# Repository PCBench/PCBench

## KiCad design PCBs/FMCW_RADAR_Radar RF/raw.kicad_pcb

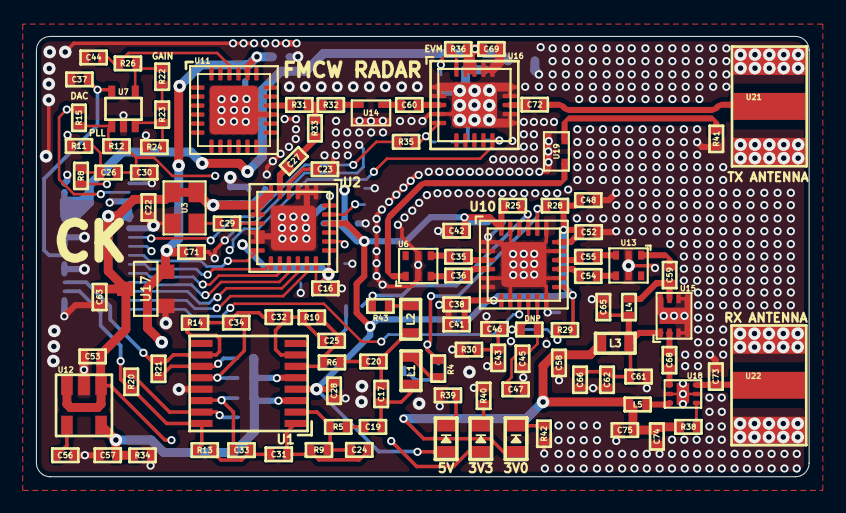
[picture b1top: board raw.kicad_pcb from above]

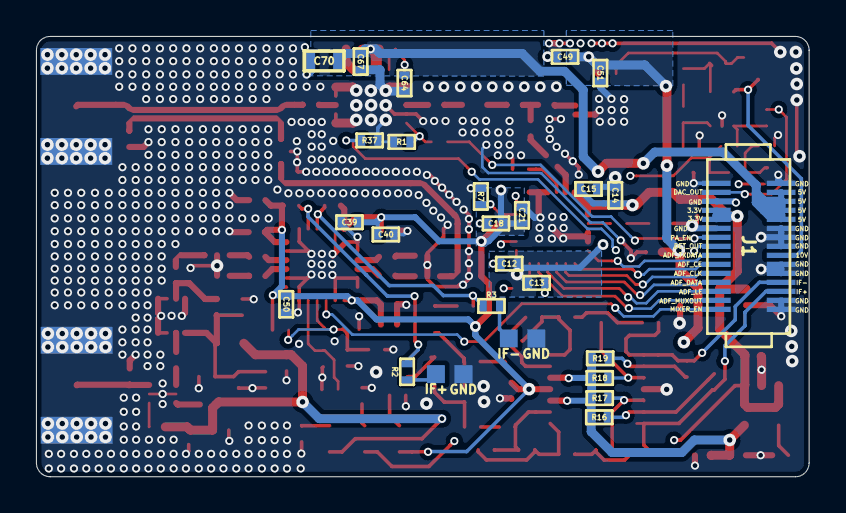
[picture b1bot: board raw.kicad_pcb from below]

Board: 4 copper layers, 42.9 x 24.5 mm, 143 parts (28 on the bottom side), 92 nets.

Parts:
3V0, 3V3, 5V: Led_Diode; Diode_0603
C12, C13, C14, C21, C22, C28, C37, C38, C39, C40, C43, C45, C46, C48, C50, C51, C52, C53, C64, C67, C69, C74, C75: 100nF; SMD_0402
C15, C16, C18, C59, C68: 18pF; SMD_0402
C17: 2.2nF; SMD_0402
C19, C20, C26: 330nF; SMD_0402
C23, C41, C42, C47, C65: 100pF; SMD_0402
C24, C25, C35, C36, C54, C55, C62: 10pF; SMD_0402
C27: 2pF; SMD_0402
C29, C31, C32, C33, C34, C44: 470pF; SMD_0402
C30, C56, C61: 10nF; SMD_0402
C49, C57, C63, C71: 2.2uF; SMD_0402
C58, C66: DNP; SMD_0402
C60, C72: 1000pF; SMD_0402
C70: 10uF; SMD_0603
C73: 0.5pF; SMD_0402
DNP: DNP; SMD_0402
GND: GND; SolderPad_1_1.5mm_SMD_Rectangle
GND#2: GND; SolderPad_1_1.5mm_SMD_Rectangle
IF+: IF+_PAD; SolderPad_1_1.5mm_SMD_Rectangle
IF-: IF-_PAD; SolderPad_1_1.5mm_SMD_Rectangle
J1: Connector_02x15; PinHeader_2x15_DF12B(5.0)-30DP-0.5V(86)
L1, L2: 2.2uH; SMD_0603
L3: BLM18PG181SN1D; SMD_0603
L4: LQW15AN9N9J80D; SMD_0402
L5: 0.6nH; SMD_0402
R1, R16, R19, R29, R39, R40, R42: 1K; SMD_0402
R2, R3, R15, R30: DNP; SMD_0402
R4, R12, R22, R35, R43: 0; SMD_0402
R5, R6: 549; SMD_0402
R7: 5.49K; SMD_0402
R8: 69.8; SMD_0402
R9, R10, R34: 10K; SMD_0402
R11: 240; SMD_0402
R13, R14: 910; SMD_0402
R17, R18: 130; SMD_0402
R20, R21: 4.99K; SMD_0402
R23, R24, R26: 4.7K; SMD_0402
R25, R28, R41: 50; SMD_0402
R31, R32, R33: 18; SMD_0402
R36: 0 to 27; SMD_0402
R37: 30K; SMD_0402
R38: 100; SMD_0402
U1: LT6232; SSOP16_3.9x4.9mm_P0.635mm
U2: ADF4158; LFCSP24_4x4mm_P0.5mm_1EXP_2.5x2.5mm
U3: SG-210STF; Crystal_2.5x2mm
U4, U9, U23: MITERED_BEND; Mitered_Bend_0.34mm_90
U5: MITERED_BEND; Mitered_Bend_0.34mm_45
U6, U13: 5400BL15B050E; Balun_5400BL15B050E
U7: TLV172; SC70_5
U8: MITERED_BEND; Mitered_Bend_0.34mm_45_Mirrored
U10: ADL5801; LFCSP24_4x4mm_P0.5mm_1EXP_2.5x2.5mm
U11: HMC431LP4; QFN24_4x4mm_P0.5mm_1EXP_2.7x2.7mm
U12: LDS3985; SOT23_5
U14, U19: PAT1220-C-6DB; PAT1220_6dB
U15: TRF37A73; WSON8_2x2mm_P0.5mm_1EXP_0.9x1.6mm
U16: TQP5523; QFN20_4x4mm_P0.5mm_1EXP_2.5x2.5mm
U17: MCP1700; SOT23_3
U18: SKY65404; SKY65404_31
U20: Directional_Coupler; Directional_Coupler_15dB
U21, U22: SMA_Connector

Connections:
25MHz: C29.1, U2.9
+2V5: C57.1, R16.2, R17.2, R18.1, R19.2, R34.1, U1.3, U1.5, U12.5
+3V0: 3V0.2, C49.1, C51.1, C58.1, C71.1, C74.1, C75.1, L3.1, L5.2, R38.1, U11.20, U17.2
+3V3: 3V3.2, C12.1, C13.1, C14.1, C15.1, C16.1, C22.1, C53.1, C63.1, J1.4, J1.5, U2.6, U2.7, U2.8, U2.18, U2.19, U3.1, U3.4, U12.1, U12.3, U17.3
+5V: 5V.2, C18.1, C21.1, C28.2, C38.2, C39.2, C40.2, C41.2, C42.2, C48.2, C50.2, C52.1, C67.2, C69.2, C70.2, J1.26, J1.27, J1.28, J1.29, R25.1, R28.2, R29.1, R36.1, U1.4, U2.22, U10.7, U10.13, U10.18, U10.24, U16.18, U16.19
+10V: C37.1, J1.22, U7.5
ADF_CE: J1.10, U2.13
ADF_CLK: J1.11, U2.14
ADF_DATA: J1.12, U2.15
ADF_LE: J1.13, U2.16
ADF_MUXOUT: J1.14, U2.17
ADF_TXDATA: J1.9, U2.12
DAC_OUT1: J1.2, R15.1
DET_OUT: J1.8, R37.1, U16.10
GND: C12.2, C13.2, C14.2, C15.2, C16.2, C18.2, C21.2, C22.2, C23.2, C28.1, C30.2, C37.2, C38.1, C39.1, C40.1, C41.1, C42.1, C43.1, C44.2, C45.1, C46.1, C47.1, C48.1, C49.2, C50.1, C51.2, C52.2, C53.2, C56.2, C57.2, C58.2, C61.2, C62.2, C63.2, C64.2, C65.2, C66.2, C67.1, C69.1, C70.1, C71.2, C73.2, C74.2, C75.2, GND.1, GND#2.1, J1.1, J1.3, J1.6, J1.16, J1.17, J1.20, J1.21, J1.23, J1.24, J1.25, J1.30, R1.2, R7.2, R11.1, R24.2, R30.2, R34.2, R37.2, R39.2, R40.2, R41.2, R42.2, U1.13, U2.1, U2.2, U2.3, U2.10, U2.11, U2.25, U3.2, U6.2, U6.5, U7.2, U10.1, U10.2, U10.5, U10.6, U10.8, U10.12, U10.14, U10.17, U10.19, U10.23, U10.25, U11.15, U11.25, U12.2, U13.2, U13.5, U14.3, U15.3, U15.4, U15.5, U15.6, U15.8, U15.9, U16.1, U16.2, U16.4, U16.11, U16.12, U16.14, U16.15, U16.16, U16.17, U16.21, U17.1, U18.2, U18.5, U18.7, U19.3, U21.2, U21.3, U21.4, U21.5, U22.2, U22.3, U22.4, U22.5
IF+: R2.1, R4.1, R28.1, U10.20
IF-: R3.2, R25.2, R43.2, U10.21
IFN_Filtered: J1.19, R14.2, R21.1, U1.10
IFP_Filtered: J1.18, R13.1, R20.1, U1.16
MIXER_ENB: J1.15, U10.9
MIXER_LO: U4.2, U6.1
unnamed: C17.1, C19.2, L1.2
unnamed: C17.2, C20.2, L2.2
unnamed: C19.1, R5.1
unnamed: C20.1, R6.1
unnamed: C23.1, U2.4
unnamed: C24.1, C31.2, R9.2, U1.1
unnamed: C24.2, R5.2, R9.1, U1.2
unnamed: C25.1, C32.2, R10.2, U1.7
unnamed: C25.2, R6.2, R10.1, U1.6
unnamed: C26.1, C30.1, R12.1, U2.24
unnamed: C26.2, R8.2, R11.2
unnamed: C27.1, U2.5
unnamed: C27.2, R33.2
unnamed: C29.2, U3.3
unnamed: C31.1, C33.2, R13.2
unnamed: C32.1, C34.2, R14.1
unnamed: C33.1, R17.1, U1.14
unnamed: C34.1, R18.2, U1.12
unnamed: C35.1, U10.3
unnamed: C35.2, U6.4
unnamed: C36.1, U10.4
unnamed: C36.2, U6.3
unnamed: C43.2, C46.2, DNP.2, R29.2, R30.1, U10.10
unnamed: C44.1, R26.1, U11.22
unnamed: C45.2, C47.2, DNP.1, U10.11
unnamed: C54.1, U13.4
unnamed: C55.1, U13.3
unnamed: C56.1, U12.4
unnamed: C59.1, L4.1, U15.7
unnamed: C59.2, U23.1
unnamed: C60.1, U16.3
unnamed: C60.2, U14.2
unnamed: C61.1, C62.1, C65.1, C66.1, L3.2, L4.2, U15.1
unnamed: C64.1, R36.2, U16.20
unnamed: C68.1, U18.4
unnamed: C68.2, U15.2
unnamed: C72.1, U20.1
unnamed: C72.2, U16.13
unnamed: C73.1, U18.3, U22.1
unnamed: 5V.1, R39.1
unnamed: 3V3.1, R40.1
unnamed: 3V0.1, R42.1
unnamed: L1.1, R4.2
unnamed: L2.1, R43.1
unnamed: L5.1, U18.6
unnamed: R1.1, R35.2, U16.5
unnamed: IF+.1, R2.2
unnamed: IF-.1, R3.1
unnamed: R7.1, U2.23
unnamed: R8.1, U2.20
unnamed: R12.2, R15.2, U7.1
unnamed: R16.1, R20.2, U1.15
unnamed: R19.1, R21.2, U1.11
unnamed: R22.1, R26.2, U7.4
unnamed: R22.2, R23.1
unnamed: R23.2, R24.1, U7.3
unnamed: R31.1, U11.16
unnamed: R31.2, R32.2, R33.1
unnamed: R32.1, U14.1
unnamed: R38.2, U18.1
unnamed: R41.1, U20.4
unnamed: U4.1, U8.1
unnamed: U5.1, U9.1
unnamed: U5.2, U8.2
unnamed: U13.1, U23.2
unnamed: U19.1, U20.3
unnamed: U9.2, U19.2
unnamed: U20.2, U21.1
PA_EN: J1.7, R35.1
RFIN: C54.2, U10.15
RFIP: C55.2, U10.16

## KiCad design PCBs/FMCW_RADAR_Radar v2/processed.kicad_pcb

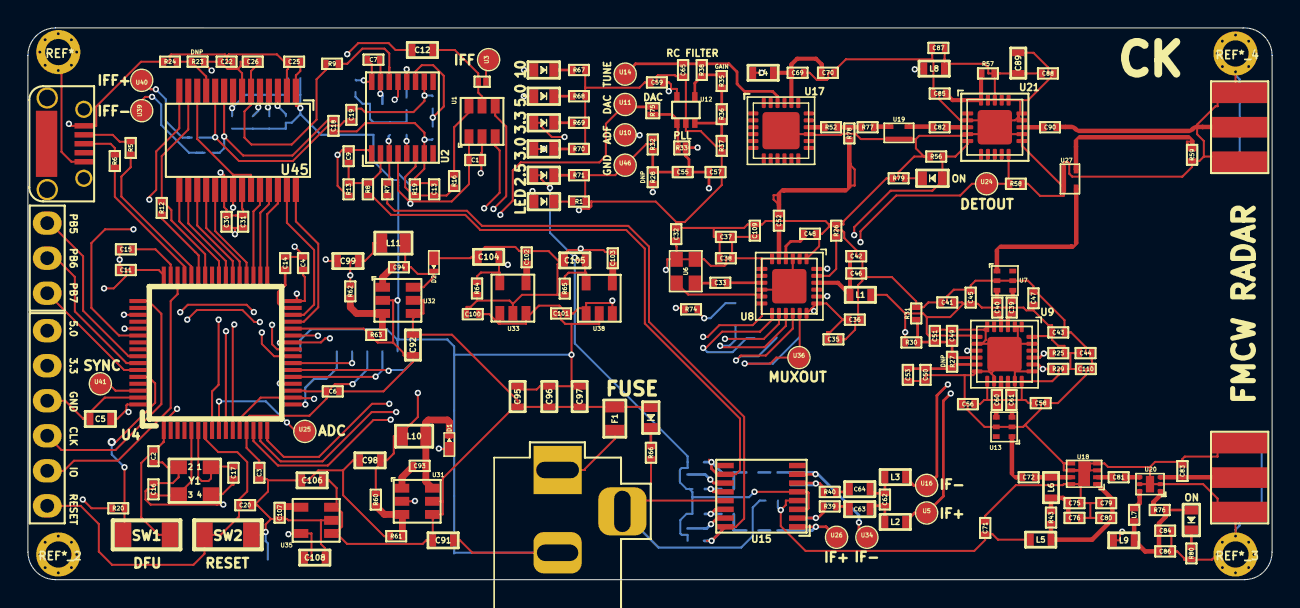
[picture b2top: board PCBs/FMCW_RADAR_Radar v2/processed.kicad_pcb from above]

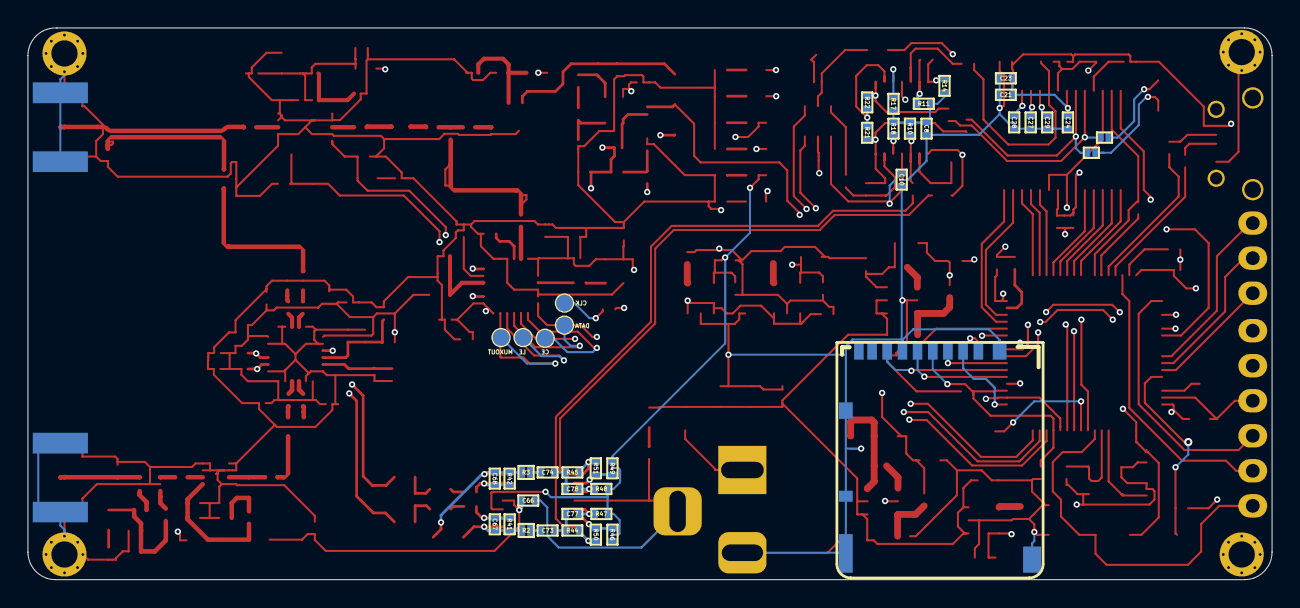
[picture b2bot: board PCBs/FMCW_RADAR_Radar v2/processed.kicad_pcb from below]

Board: 4 copper layers, 90.2 x 40.0 mm, 264 parts (42 on the bottom side), 173 nets.

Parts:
C1, C2, C3, C4, C7, C8, C10, C20, C22, C23, C26, C27, C28, C29, C30, C31, C32, C35, C36, C41, C43, C44, C46, C49, C50, C51, C56, C58, C59, C66, C70, C80, C84, C85, C86, C87, C88, C100, C101, C109, C110: 100nF; SMD_0402
C5, C12, C63, C64, C89, C91, C92, C95, C96, C97, C98, C99: 10uF; SMD_0603
C6, C11, C14, C15, C21, C69: 2.2uF; SMD_0402
C9, C13: 33pF; SMD_0402
C16, C17: 15pF; SMD_0402
C18, C19: 1uF; SMD_0402
C24, C25, C45, C47, C48, C53, C79: 100pF; SMD_0402
C33: 470pF; SMD_0402
C37, C38, C42: 18pF; SMD_0402
C39, C40, C52, C60, C61, C67, C68, C76: 10pF; SMD_0402
C55: 330nF; SMD_0402
C57, C73, C74, C75, C77, C78, C93, C94, C102, C103, C107: 10nF; SMD_0402
C62: 2.2nF; SMD_0402
C65, C71: DNP; SMD_0402
C72, C81, C82, C90: 1nF; SMD_0402
C83: 0.5pF; SMD_0402
C104, C105, C106, C108: 2.2uF; SMD_0603
D1, D2: Diode_Schottky; Diode_SDM2U30CSP_7
D3, D4, D5, D6, D7, D8, D9, D10, D11: Led_Diode; Diode_0603
F1: Fuse; SMD_0805
J1: Connector_01x03; PinHeader_1x3_P2.5mm
J2: USB_MicroB; USB_MicroB_TH
J3: Connector_01x06; PinHeader_1x6_P2.5mm
J4: DC_Jack; BarrelJack
L1, L4, L5, L8, L9: BLM18PG181SN1D; SMD_0603
L2, L3: 2.2uH; SMD_0603
L6: LQW18ANR10J00D; SMD_0603
L7: 0.6nH; SMD_0402
L10, L11: 4.7uH; SMD_0805
R1, R10, R13, R20, R30, R39, R40, R46, R49, R56, R66, R67, R68, R69, R70, R71, R79, R80: 1K; SMD_0402
R2, R3, R24, R33, R35: 0; SMD_0402
R5, R6, R12, R74: 22; SMD_0402
R7, R8, R16, R76: 100; SMD_0402
R9, R11: 2.49K; SMD_0402
R14: 49.9; SMD_0402
R15, R23, R27, R28, R31, R72, R73, R75: DNP; SMD_0402
R17, R19, R36, R37, R63: 4.7K; SMD_0402
R18, R21, R22, R41, R42, R61, R64, R65: 10K; SMD_0402
R25, R29, R59: 50; SMD_0402
R26: 5.49K; SMD_0402
R32: 240; SMD_0402
R38: 100K; SMD_0402
R43: 1.8; SMD_0402
R44, R45: 910; SMD_0402
R47, R48: 130; SMD_0402
R50, R51: 4.99K; SMD_0402
R52, R77, R78: 16.7; SMD_0402
R57: 0 to 27; SMD_0402
R58: 30K; SMD_0402
R60: 51.4K; SMD_0402
R62: 14.7K; SMD_0402
SW1: DFU_Button; Button_B3U_1000P
SW2: Reset_Button; Button_B3U_1000P
U1: MCP4022; SOT23_6
U2: LT1817GN; SSOP16_3.9x4.9mm_P0.635mm
U3, U5, U10, U11, U14, U16, U24, U26, U34, U36, U39, U40, U41, U46: Check_Point; SolderPad_1_1.5mm_SMD_Circle
U4: STM32F405; LQFP64_10x10mm_P0.5mm
U6: SG-210STF; Crystal_2.5x2mm
U7, U13: 5400BL15B050E; Balun_5400BL15B050E
U8: ADF4158; LFCSP24_4x4mm_P0.5mm_1EXP_2.5x2.5mm
U9: ADL5801; LFCSP24_4x4mm_P0.5mm_1EXP_2.5x2.5mm
U12: TLV172; SC70_5
U15: LT6232; SSOP16_3.9x4.9mm_P0.635mm
U17: HMC431LP4; QFN24_4x4mm_P0.5mm_1EXP_2.7x2.7mm
U18: TRF37A75; WSON8_2x2mm_P0.5mm_1EXP_0.9x1.6mm
U19, U27: PAT1220-C-6DB; PAT1220_6dB
U20: SKY65404; SKY65404_31
U21: TQP5523; QFN20_4x4mm_P0.5mm_1EXP_2.5x2.5mm
U22, U30: SMA_Connector
U23, U28, U42, U43, U44: MITERED_BEND; Mitered_Bend_0.33mm_90
U25: ADC_Connector; SolderPad_1_1.5mm_SMD_Circle
U29: Directional_Coupler; Directional_Coupler_15dB
U31, U32: AP3211; SOT23_6
U33, U38: LDS3985; SOT23_5
U35: LP298XS; SOT23_5
U37: MicroCard; MICROCARD_DM3AT_SF_PEJM5
U45: MAX1426; SSOP28_5.3x10.2mm_P0.65mm
U47, U48, U49, U50, U51: Check_Point; SolderPad_1_1.2mm_SMD_Circle
Y1: 8MHz; Crystal_3.2x2.5mm

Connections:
2.5: C105.1, D8.2, R46.2, R47.2, R48.1, R49.2, R65.1, U15.3, U15.5, U38.5
3.0: C104.1, D7.2, L4.2, R64.1, U33.5
3.3: C2.1, C3.1, C4.1, C5.1, C6.1, C11.1, C30.2, C31.2, C32.1, C35.1, C36.1, C37.1, C38.1, C99.1, C100.1, C101.1, C109.1, D6.2, J3.2, L9.1, L11.2, R62.1, SW1.2, U4.1, U4.13, U4.19, U4.32, U4.48, U4.64, U6.1, U6.4, U8.6, U8.7, U8.8, U8.18, U8.19, U33.1, U33.3, U37.4, U38.1, U38.3, U45.20, U45.22
5: C1.1, C10.1, C21.1, C22.1, C23.1, C24.1, C25.1, C41.2, C43.2, C44.2, C45.2, C47.2, C56.2, C58.1, C66.2, C71.1, C98.1, C110.2, D5.2, J2.1, J3.1, L1.2, L5.1, L8.1, L10.2, R24.2, R25.1, R29.2, R30.1, R60.1, U1.1, U2.4, U9.7, U9.13, U9.18, U9.24, U15.4, U45.2, U45.8
10: C59.1, C108.1, D4.2, U12.5, U35.5
+Battery: C91.1, C92.1, C95.1, C96.1, C97.1, C106.1, D3.2, F1.2, U31.4, U31.5, U32.4, U32.5, U35.1, U35.3
/Radar RF/LNA_3.3: C84.1, C86.1, D10.2, L7.2, L9.2, R76.1
/SYNC: U4.62, U41.1
ADC_CLK: R12.2, U4.42, U45.13
ADC_IN+: C18.1, R72.2, U45.9
ADC_IN-: C19.1, R73.1, U45.10
ADC_OE: U4.54, U45.14
ADF_CE: U4.24, U8.13, U49.1
ADF_CLK: R74.1, U8.14, U47.1
ADF_DATA: U4.53, U8.15, U48.1
ADF_LE: U4.16, U8.16, U50.1
ADF_MUXOUT: U4.15, U8.17, U36.1, U51.1
ADF_TXDATA: U4.25, U8.12
CML: C26.2, R9.1, U45.6
CMLP: R23.1, R24.1, U45.11
CM_BIAS: C8.2, R10.1, R11.2, R14.1, R17.2, R18.1
D0: U4.29, U45.28
D1: U4.30, U45.27
D2: U4.33, U45.26
D3: U4.34, U45.25
D4: U4.35, U45.24
D5: U4.36, U45.19
D6: U4.37, U45.18
D7: U4.38, U45.17
D8: U4.39, U45.16
D9: U4.40, U45.15
DAC_OUT1: R75.1, U4.20, U11.1
DET_OUT: R58.1, U4.26, U21.10, U24.1
GND: C1.2, C2.2, C3.2, C4.2, C5.2, C6.2, C8.1, C10.2, C11.2, C14.2, C15.2, C16.2, C17.2, C20.2, C21.2, C22.2, C23.2, C24.2, C25.2, C26.1, C27.2, C28.2, C29.2, C30.1, C31.1, C32.2, C35.2, C36.2, C37.2, C38.2, C41.1, C42.2, C43.1, C44.1, C45.1, C46.2, C47.1, C48.2, C49.1, C50.1, C51.1, C53.1, C56.1, C57.2, C58.2, C59.2, C65.2, C66.1, C69.2, C70.2, C71.2, C75.2, C76.2, C79.2, C80.2, C83.2, C84.2, C85.2, C86.2, C87.1, C88.1, C89.1, C91.2, C92.2, C95.2, C96.2, C97.2, C98.2, C99.2, C100.2, C101.2, C102.2, C103.2, C104.2, C105.2, C106.2, C107.1, C108.2, C109.2, C110.1, D1.2, D2.2, J2.5, J3.3, J4.2, J4.3, R1.2, R20.1, R23.2, R26.2, R31.2, R32.1, R37.2, R56.2, R58.2, R59.2, R61.2, R63.2, R64.2, R65.2, R66.2, R67.2, R68.2, R69.2, R70.2, R71.2, R79.2, R80.2, SW2.2, U1.2, U2.13, U4.12, U4.18, U4.28, U4.63, U6.2, U7.2, U7.5, U8.1, U8.2, U8.3, U8.10, U8.11, U8.25, U9.1, U9.2, U9.5, U9.6, U9.8, U9.12, U9.14, U9.17, U9.19, U9.23, U9.25, U12.2, U13.2, U13.5, U15.13, U17.15, U17.25, U18.3, U18.4, U18.5, U18.6, U18.8, U18.9, U19.3, U20.2, U20.5, U20.7, U21.1, U21.2, U21.4, U21.11, U21.12, U21.14, U21.15, U21.16, U21.17, U21.21, U22.2, U22.3, U22.4, U22.5, U27.3, U30.2, U30.3, U30.4, U30.5, U31.2, U32.2, U33.2, U35.2, U37.6, U37.10, U37.11, U38.2, U45.1, U45.7, U45.12, U45.21, U45.23, U46.1, Y1.2, Y1.4
IF+: L2.1, R29.1, U5.1, U9.20
IF-: L3.1, R25.2, U9.21, U16.1
IFF+: R7.1, R44.1, R50.1, U15.16
IFF-: R8.1, R45.2, R51.1, U15.10
LED: D11.2, U4.8
MCP_AOUT: R16.1, U1.6
MCP_CS_3V3: U1.4, U4.11
MCP_UD_3V3: U1.3, U4.10
MCP_WIN: C12.1, R15.2, U1.5
MICROCARD_CS: U4.17, U37.2
MIXER_EN: U4.14, U9.9
MIXER_LO: U7.1, U23.2
unnamed: C7.1, R14.2, U2.16
unnamed: C7.2, R11.1, U2.15
unnamed: C9.2, R8.2, R13.1, U2.2
unnamed: C9.1, C12.2, R13.2, U2.1
unnamed: C13.1, C18.2, R19.2, R21.1, U2.7
unnamed: C13.2, R16.2, R19.1, U2.6
unnamed: C14.1, U4.31
unnamed: C15.1, U4.47
unnamed: C16.1, U4.5, Y1.3
unnamed: C17.1, U4.6, Y1.1
unnamed: C19.2, R22.2, U2.10
unnamed: C27.1, U45.4
unnamed: C28.1, U45.3
unnamed: C29.1, U45.5
unnamed: C33.1, U8.9
unnamed: C33.2, U6.3
unnamed: C39.1, U9.3
unnamed: C39.2, U7.4
unnamed: C40.1, U9.4
unnamed: C40.2, U7.3
unnamed: C42.1, C46.1, L1.1, U8.22
unnamed: C48.1, U8.4
unnamed: C49.2, C51.2, R27.2, R30.2, R31.1, U9.10
unnamed: C50.2, C53.2, R27.1, U9.11
unnamed: C52.1, U8.5
unnamed: C52.2, U44.2
unnamed: C55.1, C57.1, R33.1, U8.24, U10.1
unnamed: C55.2, R28.2, R32.2
unnamed: C60.1, U13.4
unnamed: C61.1, U13.3
unnamed: C62.1, C63.2, L2.2
unnamed: C62.2, C64.2, L3.2
unnamed: C63.1, R39.1
unnamed: C64.1, R40.1
unnamed: C65.1, R38.1, U14.1, U17.22
unnamed: C67.1, R2.1, R41.2, U15.1, U26.1
unnamed: C67.2, R39.2, R41.1, U15.2
unnamed: C68.1, R3.1, R42.2, U15.7, U34.1
unnamed: C68.2, R40.2, R42.1, U15.6
unnamed: C69.1, C70.1, L4.1, U17.20
unnamed: C72.1, L6.1, U18.7
unnamed: C72.2, U42.2
unnamed: C73.1, C77.2, R44.2
unnamed: C73.2, R2.2
unnamed: C74.1, C78.2, R45.1
unnamed: C74.2, R3.2
unnamed: C75.1, C76.1, L6.2, R43.2
unnamed: C77.1, R47.1, U15.14
unnamed: C78.1, R48.2, U15.12
unnamed: C79.1, C80.1, L5.2, R43.1, U18.1
unnamed: C81.1, U20.4
unnamed: C81.2, U18.2
unnamed: C82.1, U21.3
unnamed: C82.2, U19.2
unnamed: C83.1, U20.3, U22.1
unnamed: C85.1, R57.2, U21.20
unnamed: C87.2, C88.2, C89.2, L8.2, R57.1, U21.18, U21.19
unnamed: C90.1, U29.1
unnamed: C90.2, U21.13
unnamed: C93.1, U31.1
unnamed: C93.2, D1.1, L10.1, U31.6
unnamed: C94.1, U32.1
unnamed: C94.2, D2.1, L11.1, U32.6
unnamed: C102.1, U33.4
unnamed: C103.1, U38.4
unnamed: C107.2, U35.4
unnamed: D3.1, R66.1
unnamed: D4.1, R67.1
unnamed: D5.1, R68.1
unnamed: D6.1, R69.1
unnamed: D7.1, R70.1
unnamed: D8.1, R71.1
unnamed: D9.1, R79.1
unnamed: D10.1, R80.1
unnamed: D11.1, R1.1
unnamed: F1.1, J4.1
unnamed: J2.2, R5.1
unnamed: J2.3, R6.1
unnamed: L7.1, U20.6
unnamed: R9.2, U2.14
unnamed: R7.2, R10.2, U2.3
unnamed: R12.1, U4.43
unnamed: R15.1, U3.1
unnamed: R17.1, U2.12
unnamed: R18.2, U2.5
unnamed: R20.2, SW1.1, U4.60
unnamed: R21.2, R22.1, U2.11
unnamed: R26.1, U8.23
unnamed: R28.1, U8.20
unnamed: R33.2, R75.2, U12.1
unnamed: R35.1, R38.2, U12.4
unnamed: R35.2, R36.1
unnamed: R36.2, R37.1, U12.3
unnamed: R46.1, R50.2, U15.15
unnamed: R49.1, R51.2, U15.11
unnamed: R52.1, U17.16
unnamed: R52.2, R77.1, R78.2
unnamed: R59.1, U29.4
unnamed: R60.2, R61.1, U31.3
unnamed: R62.2, R63.1, U32.3
unnamed: R72.1, U39.1
unnamed: R73.2, U40.1
unnamed: R74.2, U4.51
unnamed: R76.2, U20.1
unnamed: R77.2, U19.1
unnamed: R78.1, U43.2
unnamed: U13.1, U42.1
unnamed: U23.1, U28.1
unnamed: U4.9, U25.1
unnamed: U27.1, U29.3
unnamed: U27.2, U28.2
unnamed: U29.2, U30.1
unnamed: U43.1, U44.1
PA_EN: D9.2, R56.1, U4.27, U21.5
PB5: J1.1, U4.57
PB6: J1.2, U4.58
PB7: J1.3, U4.59
RESET: C20.1, J3.6, SW2.1, U4.7
RFIN: C60.2, U9.15
RFIP: C61.2, U9.16
SPI1_CLK: U4.21, U37.5
SPI1_MISO: U4.22, U37.7
SPI1_MOSI: U4.23, U37.3
SWDCLK: J3.4, U4.49
SWDIO: J3.5, U4.46
USB_D+: R6.2, U4.45
USB_D-: R5.2, U4.44

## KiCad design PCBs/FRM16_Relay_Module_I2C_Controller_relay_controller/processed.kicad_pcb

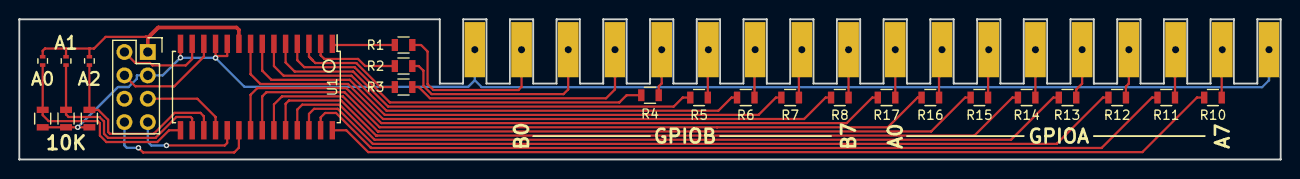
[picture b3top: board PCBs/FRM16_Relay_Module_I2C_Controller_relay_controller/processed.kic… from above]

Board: 2 copper layers, 137.2 x 15.2 mm, 30 parts (0 on the bottom side), 42 nets.

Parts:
JP1, JP2, JP3: Jumper_NO_Small; R_0402
P1, P2, P3, P4, P5, P6: CONN_01X03; card_edge_3_conductor
P7: CONN_02X04; Socket_Strip_Straight_2x04
R1, R2, R3, R4, R5, R6, R7, R8, R9, R10, R11, R12, R13, R14, R15, R16, R17, R18, R19: R; R_0805
U1: MCP23017; SOIC-28_7.5x17.9mm_Pitch1.27mm

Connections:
GND: P1.1, P4.1, P7.3, R9.2, R18.2, R19.2, U1.10, U1.11, U1.14
INTA: P7.8, U1.20
INTB: P7.7, U1.19
unnamed: JP1.2, R19.1, U1.17
unnamed: JP2.2, R18.1, U1.16
unnamed: JP3.2, R9.1, U1.15
unnamed: P1.2, R1.2
unnamed: P1.3, R2.2
unnamed: P2.1, R3.2
unnamed: P2.2, R4.2
unnamed: P2.3, R5.2
unnamed: P3.1, R6.2
unnamed: P3.2, R7.2
unnamed: P3.3, R8.2
unnamed: P4.2, R10.1
unnamed: P4.3, R11.1
unnamed: P5.1, R12.1
unnamed: P5.2, R13.1
unnamed: P5.3, R14.1
unnamed: P6.1, R15.1
unnamed: P6.2, R16.1
unnamed: P6.3, R17.1
unnamed: R1.1, U1.1
unnamed: R2.1, U1.2
unnamed: R3.1, U1.3
unnamed: R4.1, U1.4
unnamed: R5.1, U1.5
unnamed: R6.1, U1.6
unnamed: R7.1, U1.7
unnamed: R8.1, U1.8
unnamed: R10.2, U1.28
unnamed: R11.2, U1.27
unnamed: R12.2, U1.26
unnamed: R13.2, U1.25
unnamed: R14.2, U1.24
unnamed: R15.2, U1.23
unnamed: R16.2, U1.22
unnamed: R17.2, U1.21
SCL: P7.4, U1.12
SDA: P7.2, U1.13
VCC: JP1.1, JP2.1, JP3.1, P7.1, U1.9
~RST: P7.5, U1.18

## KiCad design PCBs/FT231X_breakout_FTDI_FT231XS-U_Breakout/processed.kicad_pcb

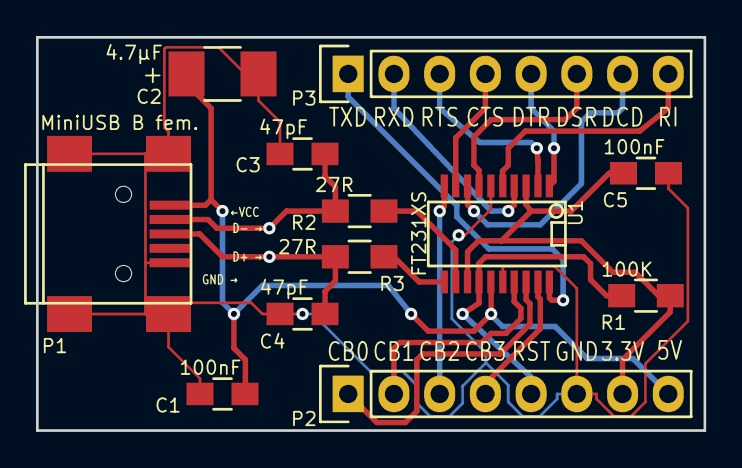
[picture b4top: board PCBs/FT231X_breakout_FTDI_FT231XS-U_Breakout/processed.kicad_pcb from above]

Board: 2 copper layers, 37.1 x 21.8 mm, 12 parts (0 on the bottom side), 20 nets.

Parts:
C1, C5: 100nF; C_0805_HandSoldering
C2: 4.7µF; C_1210_HandSoldering
C3, C4: 47pF; C_0805_HandSoldering
P1: MiniUSB B fem.; USB_Mini-B
P2, P3: CONN_01X08; Pin_Header_Straight_1x08
R1: 100K; R_0805_HandSoldering
R2, R3: 27R; R_0805_HandSoldering
U1: FT231XS; SSOP-20

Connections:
CBUS0: P2.1, U1.18
CBUS1: P2.2, U1.17
CBUS2: P2.3, U1.10
CBUS3: P2.4, U1.19
CTS: P3.4, U1.9
DCD: P3.7, U1.8
DSR: P3.6, U1.7
DTR: P3.5, U1.1
GND: C1.2, C2.2, C3.2, C4.2, C5.1, P1.5, P1.6, P2.6, U1.6, U1.16
unnamed: C3.1, P1.2, R2.2
unnamed: C4.1, P1.3, R3.2
unnamed: R2.1, U1.12
unnamed: R3.1, U1.11
RESET: P2.5, R1.2, U1.14
RI: P3.8, U1.5
RTS: P3.3, U1.2
RXD: P3.2, U1.4
TXD: P3.1, U1.20
VCC: C1.1, C2.1, P1.1, P2.8, U1.15
VCCIO: C5.2, P2.7, R1.1, U1.3, U1.13

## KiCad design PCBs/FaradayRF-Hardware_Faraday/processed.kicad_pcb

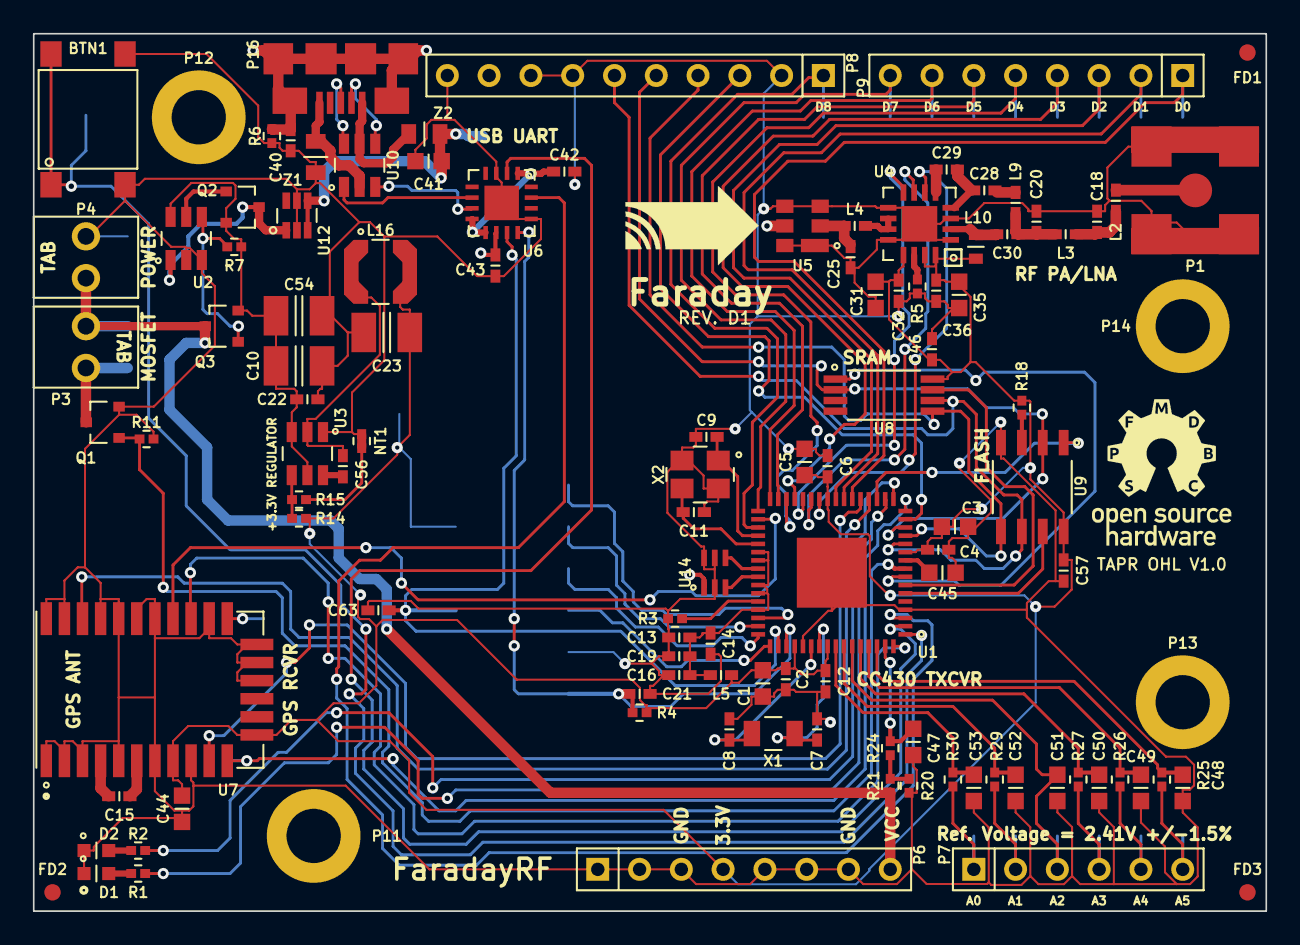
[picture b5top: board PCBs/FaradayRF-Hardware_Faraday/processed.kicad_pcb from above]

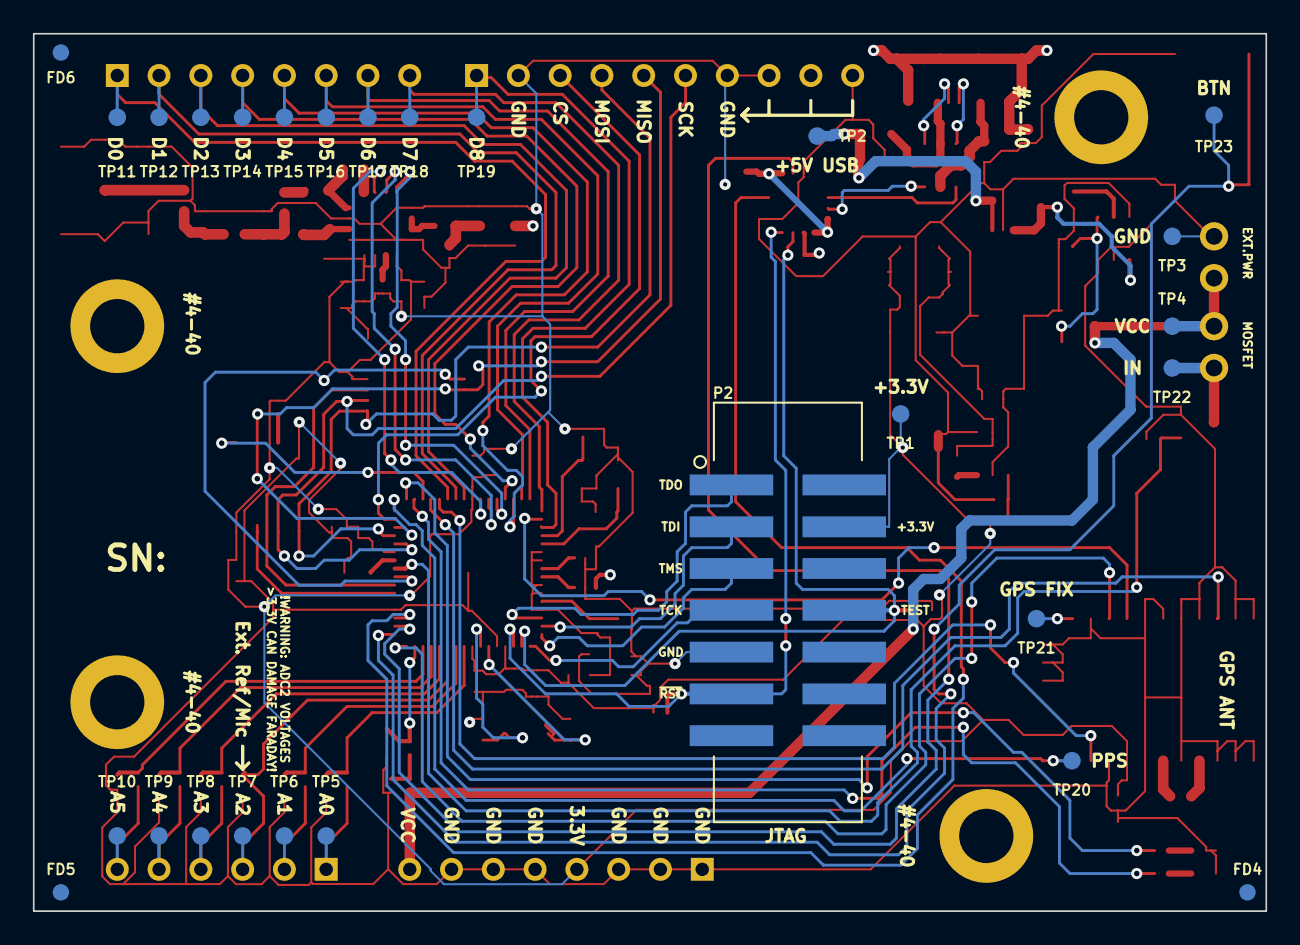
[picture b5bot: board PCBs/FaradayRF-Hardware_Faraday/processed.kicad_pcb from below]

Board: 4 copper layers, 74.9 x 53.3 mm, 141 parts (27 on the bottom side), 97 nets.

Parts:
BTN1: DNP; PTS645-SMD
C1, C3, C5, C31, C35, C41, C44, C47, C48, C49, C50, C52, C53: 1uF; C0603
C2, C4, C6, C12, C13, C16, C32, C36, C40, C42, C43, C46, C56: 0.1uF; C0402
C7, C8, C22, C57: DNP; C0402
C9, C11: 30pF; C0402
C10, C54: 10uF; C1210
C14, C15, C19, C28, C29, C63: 12pF; C0402
C18: 7.5pF; C0402
C20: 3.3pF; C0402
C21: 2.2nF; C0402
C23: 47uF; C1210
C25: 0.8pF; C0402
C30: 47pF; C0402
C45: 470nF; C0603
C51: DNP; C0603
D1, D2: LED-IPC; LGL29K
FD1, FD2, FD3, FD4, FD5, FD6: FIDUCIAL; FD1
G1: OSHW
G2: FARADAYRF; faradayRF
L2: 9.1nH; L0402
L3: 2.9nH; L0402
L4: 10nH; L0402
L5: BLM15HG102SN1D; L0402
L9: 7.5nH; L0402
L10: 22nH; L0603
L16: 4.7uH; LPS4018
NT1: NETTIE; NETTIE-0402
P1: RF_FEMALE; CONSMA001-SMD-G
P2: DNP; 2514-6002UB
P3, P4: 22232021
P6, P9: DNP; SIL-8
P7: DNP; SIL-6
P8: DNP; SIL-10
P11, P12, P13, P14: DNP; MTH-4-40-Tight
P16: USB-MICRO-B; 10118192-0001LF
Q1: IRLML6346TRPBF; SOT23-NXP
Q2, Q3: PMV48XP; SOT23-NXP
R1, R2: 360; R0402
R3, R4, R7: 56K; R0402
R5, R20: 3.3K; R0402
R6: 1M; R0402
R11, R15, R24, R25, R26, R27, R29, R30: 10K; R0402
R14, R21: 33.2K; R0402
R18: DNP; R0402
TP1, TP2, TP3, TP4, TP5, TP6, TP7, TP8, TP9, TP10, TP11, TP12, TP13, TP14, TP15, TP16, TP17, TP18, TP19, TP20, TP21, TP22, TP23: TEST-POINT; TEST-POINT-42MIL
U1: CC430F6137; RGC
U2: LTC4412; TSOT23-6
U3: TPS562201DDCR; TSOT23-6
U4: CC1190; RGV
U5: SF2049E
U6: FT230XQ-R; QFN-16-4x4
U7: M10478-A2
U8: 23K256T-I/ST; TSSOP8
U9: DNP; SOIC8-150MIL
U10: NUF2101MT1G; TSOT23-6
U12: MIC94072YC6; SC70-6
U14: 0915BM15A0001E
X1: ST3215SB32768H5HPWAA
X2: ABM8G-26.000MHZ-18-D2Y-T; ABM8G
Z1, Z2: MI0805K400R-10; L0805

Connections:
+3.3V: C1.1, C2.1, C3.1, C4.1, C5.1, C6.1, C12.1, C23.1, C31.2, C32.2, C35.2, C36.2, C44.1, C46.1, C57.1, L5.2, L10.1, L16.2, P2.4, P6.4, R4.1, R14.1, R18.2, TP1.1, U1.11, U1.25, U1.52, U1.56, U4.13, U4.15, U4.16, U7.8, U7.12, U8.8, U9.8
+5V: C41.1, C43.1, TP2.1, U6.10, U12.3, U12.4, Z2.2
/CC430/DIGITAL_IO_0: P9.1, TP11.1, U1.22
/CC430/DIGITAL_IO_1: P9.2, TP12.1, U1.23
/CC430/DIGITAL_IO_2: P9.3, TP13.1, U1.24
/CC430/DIGITAL_IO_3: P9.4, TP14.1, U1.29
/CC430/DIGITAL_IO_4: P9.5, TP15.1, U1.30
/CC430/DIGITAL_IO_5: P9.6, TP16.1, U1.31
/CC430/DIGITAL_IO_6: P9.7, TP17.1, U1.32
/CC430/DIGITAL_IO_7: P9.8, TP18.1, U1.33
/CC430/DIGITAL_IO_8: P8.1, TP19.1, U1.35
/CC430/GPS-PPS: TP20.1, U1.16, U7.11
/CC430/GPS-RX: U1.34, U7.21
/CC430/GPS-TX: U1.64, U7.20
/CC430/MEM ~CS0~: U1.8, U8.1
/CC430/MEM ~CS1~: U1.19, U9.1
/CC430/MEM ~HOLD0~: U1.7, U8.7
/CC430/MEM ~HOLD1~: U1.6, U9.7
/CC430/MOSFET_CNTL: Q1.1, R11.1, U1.9
/CC430/P1_7: BTN1.1, BTN1.2, TP23.1, U1.1
/CC430/P2_1: C47.1, R24.2, U1.63
/CC430/P2_2: C48.1, R25.2, U1.62
/CC430/P2_3: C49.1, R26.2, U1.61
/CC430/P2_4: C50.1, R27.2, U1.60
/CC430/P2_6: C52.1, R29.2, U1.58
/CC430/P2_7: C53.1, R30.2, U1.57
/CC430/P3_6: R1.1, U1.18
/CC430/P3_7: R2.1, U1.17
/CC430/P5_0: C7.1, U1.55, X1.1
/CC430/P5_1: C8.1, U1.54, X1.2
/CC430/RF-PWR: C13.1, C14.1, C16.1, C19.1, L5.1, U1.38, U1.39, U1.42, U1.43, U1.45
/CC430/RF_N: U1.41, U14.3
/CC430/RF_P: U1.40, U14.4
/CC430/TCK: P2.7, U1.49
/CC430/TDI: P2.3, U1.47
/CC430/TDO: P2.1, U1.46
/CC430/TEST: C63.1, P2.8, U1.50, U6.11
/CC430/TMS: P2.5, U1.48
/CC430/~RST~: C21.1, P2.11, R4.2, U1.51, U6.12
/GPS/HRST: U1.21, U7.10
/GPS/STDBY: U1.20, U7.26
/Power Supply/3V3_SW: C56.2, L16.1, U3.2
/RF Front End/50Z-1: C25.1, L4.2, U5.2
/RF Front End/50Z-2: L4.1, U4.10, U4.11
/RF Front End/50Z_3: C30.2, L10.2, U4.2
/RF Front End/50Z_4: C20.1, C30.1, L3.2, L9.1
/RF Front End/50Z_5: C18.1, L2.2, L3.1
/RF Front End/CC1190-CC430-RF: U5.5, U14.1
/RF Front End/HGM_Select: U1.26, U4.6
/RF Front End/LNA_Enable: U1.27, U4.7
/RF Front End/PA_Enable: U1.28, U4.8
/RF Front End/RF_IN_OUT_Antenna: L2.1, P1.1
/Shield Connector/AD_0: P7.1, R30.1, TP5.1
/Shield Connector/AD_1: P7.2, R29.1, TP6.1
/Shield Connector/AD_2: C51.1, P7.3, TP7.1, U1.59
/Shield Connector/AD_3: P7.4, R27.1, TP8.1
/Shield Connector/AD_4: P7.5, R26.1, TP9.1
/Shield Connector/AD_5: P7.6, R25.1, TP10.1
/Shield Connector/CONN_CS: P8.3, U1.15
/Shield Connector/CONN_MISO/SCL: P8.5, U1.14, U8.2, U9.2
/Shield Connector/CONN_MOSI/SDA: P8.4, U1.13, U8.5, U9.5
/Shield Connector/CONN_SCK: P8.6, U1.12, U8.6, U9.6
/Shield Connector/MOSFET Channel/IN: P3.2, Q1.3, TP22.1
/Shield Connector/VCC-MON: R20.1, R21.2, R24.1
/USB to Serial/RXD: U1.2, U6.2
/USB to Serial/TXD: U1.3, U6.15
DGND: BTN1.3, BTN1.4, C1.2, C2.2, C3.2, C4.2, C5.2, C6.2, C7.2, C8.2, C9.2, C10.2, C11.2, C12.2, C13.2, C14.2, C16.2, C18.2, C19.2, C20.2, C21.2, C22.2, C23.2, C25.2, C31.1, C32.1, C35.1, C36.1, C40.2, C41.2, C42.2, C43.2, C44.2, C45.2, C46.2, C47.2, C48.2, C49.2, C50.2, C51.2, C52.2, C53.2, C54.2, C57.2, C63.2, D1.1, D2.1, NT1.1, P1.2, P2.9, P4.2, P6.1, P6.2, P6.3, P6.5, P6.6, P6.7, P8.2, P8.7, P8.8, P8.9, P8.10, Q1.2, R3.2, R5.2, R6.1, R11.2, R20.2, TP3.1, U1.4, U1.53, U1.65, U2.2, U2.3, U3.1, U4.1, U4.3, U4.9, U4.12, U4.17, U5.1, U5.3, U5.4, U5.6, U6.3, U6.13, U6.17, U7.1, U7.2, U7.3, U7.5, U7.7, U7.9, U7.15, U7.16, U7.17, U7.19, U7.22, U7.23, U7.24, U7.25, U7.27, U7.28, U9.4, U12.2, U12.5, U14.2, U14.5, U14.6, X2.2, X2.4, Z1.2
GNDPWR: C40.1, P11.1, P12.1, P13.1, P14.1, P16.6, R6.2
unnamed: C45.1, U1.10
unnamed: D1.2, R1.2
unnamed: D2.2, R2.2
unnamed: R3.1, U1.44
unnamed: C9.1, U1.36, X2.1
unnamed: C11.1, U1.37, X2.3
unnamed: C10.1, C22.1, C54.1, Q2.2, Q3.2, R7.1, U2.6, U3.3, U3.5
unnamed: C56.1, U3.6
unnamed: R14.2, R15.1, U3.4
unnamed: NT1.2, R15.2
unnamed: Q2.1, U2.5
unnamed: Q3.1, R7.2, U2.4
unnamed: Q2.3, U2.1, U12.1
unnamed: C28.2, C29.1, U4.4
unnamed: R5.1, U4.14
unnamed: C29.2, U4.5
unnamed: C28.1, L9.2
unnamed: P16.1, U10.5, Z2.1
unnamed: U6.6, U10.1
unnamed: P16.3, U10.6
unnamed: P16.2, U10.4
unnamed: U6.7, U10.3
unnamed: P16.5, U10.2, Z1.1
unnamed: C42.1, U6.1, U6.8, U6.9
unnamed: TP21.1, U7.18
unnamed: C15.2, U7.6
unnamed: C15.1, U7.4
unnamed: R18.1, U9.3
VCC: P3.1, P4.1, P6.8, Q3.3, R21.1, TP4.1

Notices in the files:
PCBs/FlashProgrammer_flash_programmer/processed.kicad_pcb:
Copyright 2017 John DiSanti
Copyright and related rights are licensed under the Solderpad Hardware License, Version 0.51 (the \"License\");
http://solderpad.org/licenses/SHL-0.51. Unless required by applicable law or agreed to in writing, software,
hardware and materials distributed under this License is distributed on an \"AS IS\" BASIS, WITHOUT WARRANTIES
